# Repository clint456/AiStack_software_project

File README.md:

# 毕业设计项目：ChatGpt对话机器人
## 参考日本开源项目
> [stack-chan](https://github.com/meganetaaan/stack-chan.git)
>
> [Gpt 对话机器人 AI_StackChan2](https://github.com/robo8080/AI_StackChan2)

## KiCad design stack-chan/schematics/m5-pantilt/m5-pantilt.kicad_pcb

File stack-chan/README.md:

# 堆栈陈

[](https://github.com/meganetaaan/stack-陈/动作/工作流程/build.yml）

[日本语](./README_ja.md)

Stack-chan是一个JavaScript驱动的M5Stack嵌入式超级卡哇伊机器人。

*视频（附英文字幕）：https://youtu.be/fZb_mF08xV0
*官方主题标签：[`#stackchan` | `#ｽﾀｯｸﾁｬﾝ`（日文）](https://twitter.com/search?q=%23stackchan%20OR%20%23%EF%BD%BD%EF%BE%80%EF%BD%AF%EF %BD%B8%EF%BE%81%EF%BD%AC%EF%BE%9D）。

＃＃ 特征

*:neutral_face: 显示可爱的脸
*:smile: 表情（高兴、生气、悲伤等）
*:smiley_cat: 自定义脸部
*:眼睛：扫视/凝视/凝视
*:speech_balloon: 说些话
*:灯泡: 插件 M5Units
*:cyclone: 驱动串行(TTL)/PWM伺服系统
*:game_die: 自己制作应用程序

＃＃ 内容

该存储库包含机器人的所有组件。

*__firmware__ : 固件的源代码。
*__case__ ：案例的立体光刻（STL）。
*__schematics__ ：原理图和电路板布局数据。

＃＃ 安装

### 组装板

*请参阅 [schematics/README.md](./schematics/README.md) 和 [case/README.md](./case/README.md)
*或者您可以获得预组装模块（即将推出）
### 将固件闪存到 M5Stack

*请参阅[固件/README.md](./firmware/README.md)

＃＃ 贡献

__功能请求/错误报告__非常受欢迎！请参阅[问题](https://github.com/meganetaaan/stack-chan/issues)页面来发布一些内容。

__想成为赞助商__吗？这将是我莫大的荣幸。请访问我的[赞助商](https://github.com/sponsors/meganetaaan/) 页面。

＃＃ 执照

该存储库的资源根据 Apache 2.0 版许可证分发。
请参阅[许可证](./许可证)。

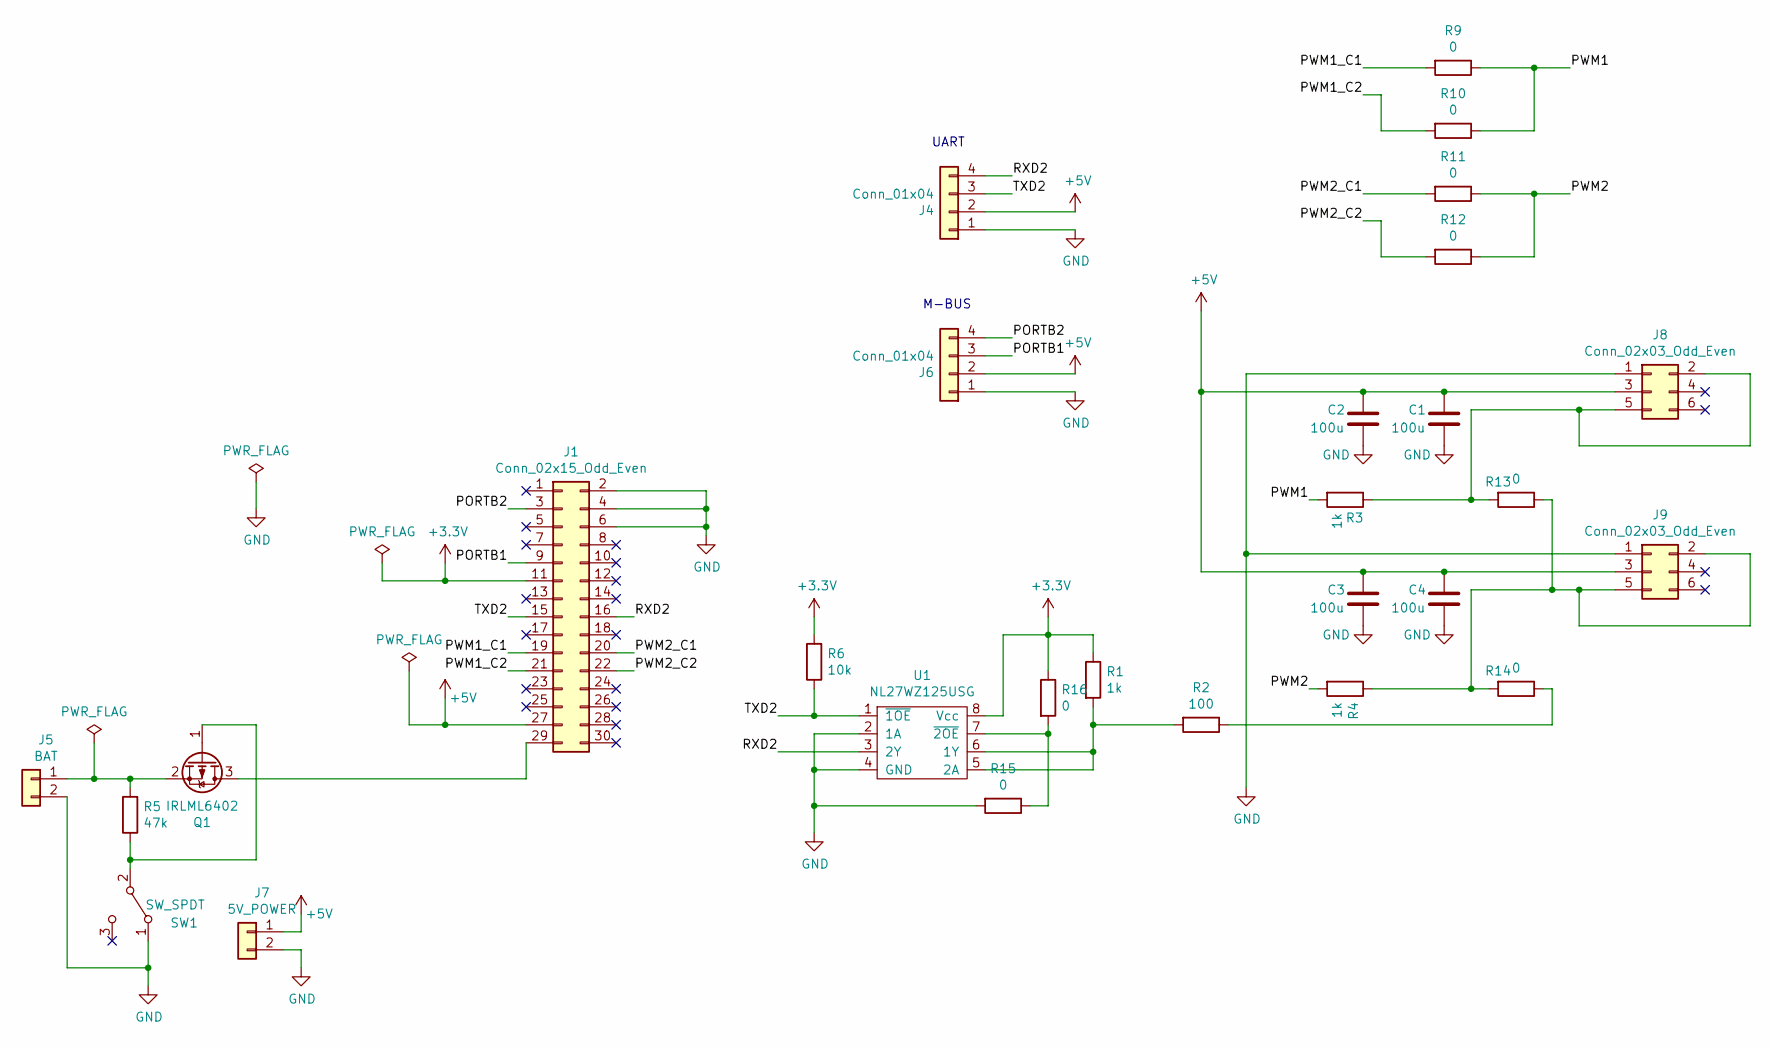
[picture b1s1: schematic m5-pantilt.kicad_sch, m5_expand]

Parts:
C1, C2, C3, C4: 100u; C_1206_3216Metric_Pad1.42x1.75mm_HandSolder
J1: Conn_02x15_Odd_Even; PinHeader_2x15_P2.54mm_Vertical_SMD
J4, J6: Conn_01x04; JST_PH_S4B-PH-K_1x04_P2.00mm_Horizontal
J5: BAT; JST_PH_B2B-PH-K_1x02_P2.00mm_Vertical
J7: 5V_POWER; JST_XH_B2B-XH-A_1x02_P2.50mm_Vertical
J8, J9: Conn_02x03_Odd_Even; PinHeader_2x03_P2.54mm_Vertical
Q1: IRLML6402; SOT-23
R1, R3, R4: 1k; R_0603_1608Metric_Pad1.05x0.95mm_HandSolder
R2: 100; R_0603_1608Metric_Pad1.05x0.95mm_HandSolder
R5: 47k; R_0603_1608Metric_Pad1.05x0.95mm_HandSolder
R6: 10k; R_0603_1608Metric_Pad1.05x0.95mm_HandSolder
R9, R10, R11, R12, R13, R14, R15, R16: 0; R_0603_1608Metric_Pad1.05x0.95mm_HandSolder
SW1: SW_SPDT; SW_CuK_OS102011MA1QN1_SPDT_Angled
U1: NL27WZ125USG

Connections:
+3V3: J1.11, R1.1, R6.2, R16.1, U1.8 (Vcc)
+5V: C1.2, C2.2, C3.1, C4.2, J1.27, J4.2, J6.2, J7.1, J8.3, J9.3; also elsewhere on the board
/PORTB1: J1.9, J6.3
/PORTB2: J1.3, J6.4
/PWM1: R3.2, R9.1, R10.1
/PWM1_C1: J1.19, R9.2
/PWM1_C2: J1.21, R10.2
/PWM2: R4.2, R11.1, R12.1
/PWM2_C1: J1.20, R11.2
/PWM2_C2: J1.22, R12.2
/RXD2: J1.16, J4.4, U1.3 (2Y)
/TXD2: J1.15, J4.3, R6.1, U1.1 (~1OE)
GND: C1.1, C2.1, C3.2, C4.1, J1.2, J1.4, J1.6, J4.1, J5.2, J6.1, J7.2, J8.1, J9.1, R15.2, SW1.1 (A), U1.2 (1A), U1.4 (GND); also elsewhere on the board
unnamed: J1.29, Q1.3 (D)
unnamed 14: J8.2, J8.5, R3.1, R13.2; also elsewhere on the board
unnamed 15: J9.2, J9.5, R4.1, R13.1, R14.2; also elsewhere on the board
unnamed: J5.1, Q1.2 (S), R5.2
unnamed: Q1.1 (G), R5.1, SW1.2 (B)
unnamed: R2.1, R14.1
unnamed: R1.2, R2.2, U1.5 (2A), U1.6 (1Y)
unnamed: R15.1, R16.2, U1.7 (~2OE)

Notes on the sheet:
M-BUS
UART

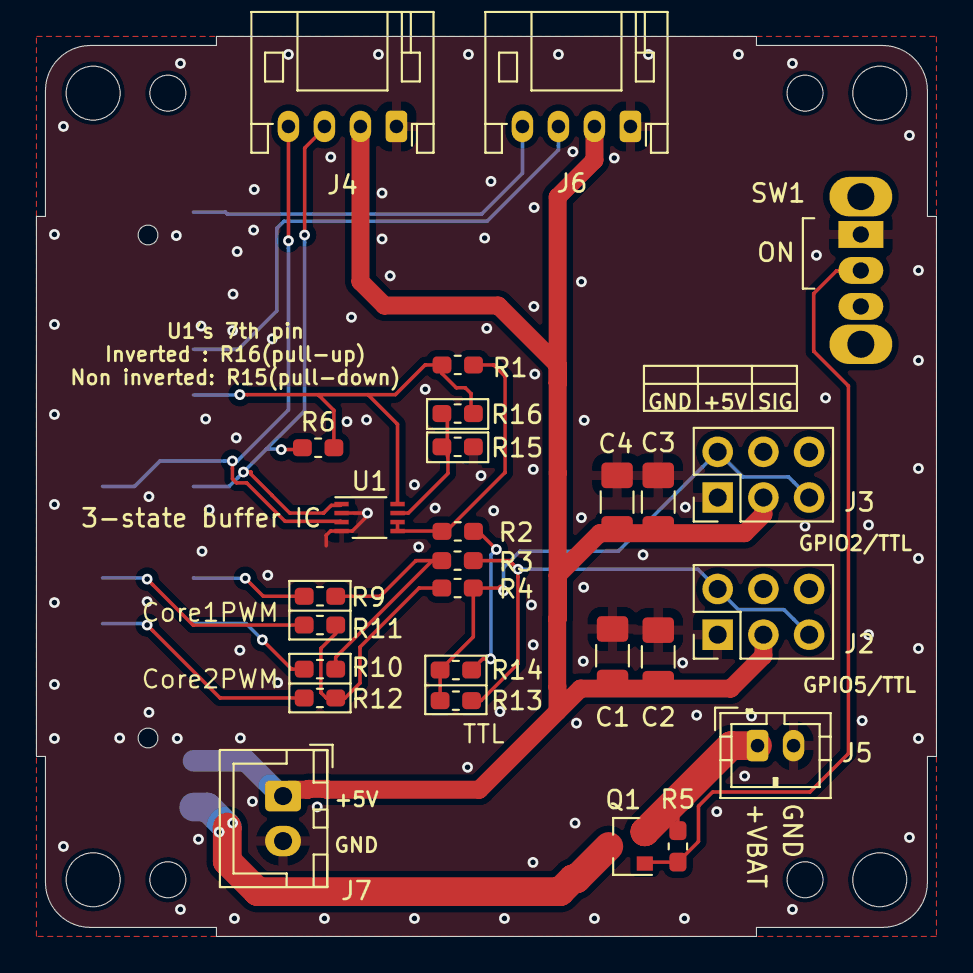
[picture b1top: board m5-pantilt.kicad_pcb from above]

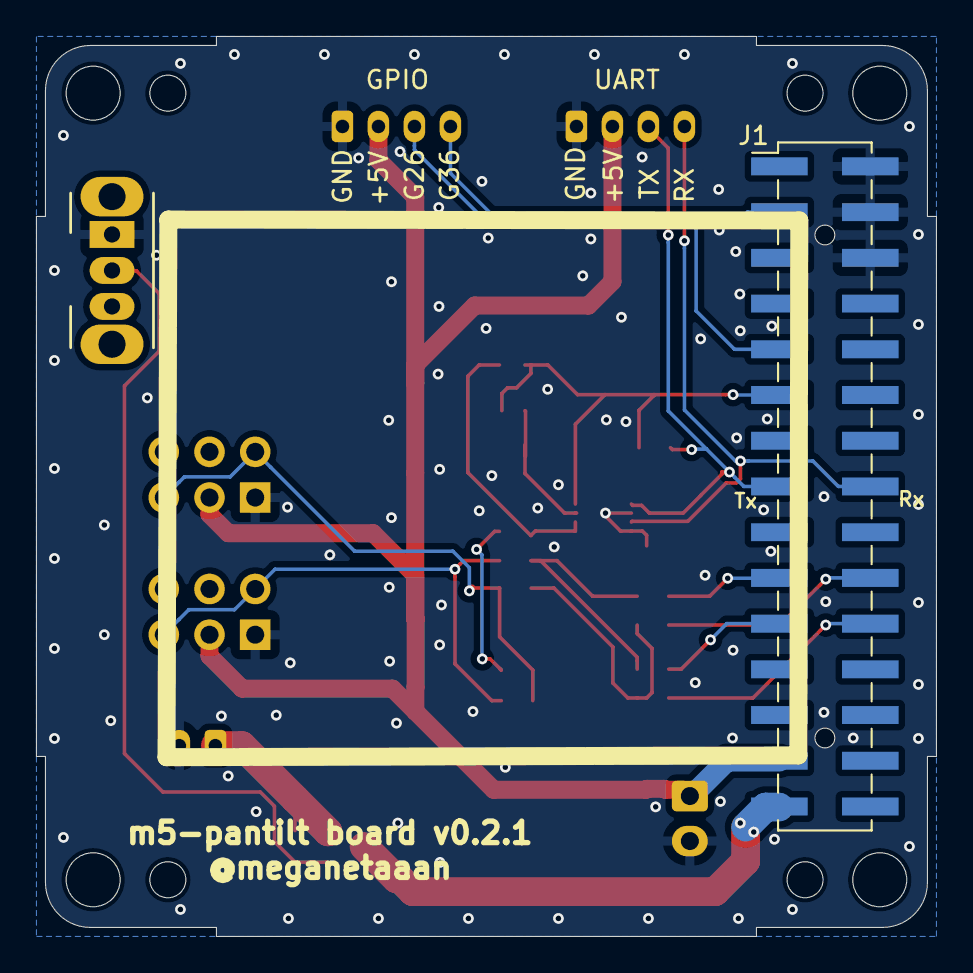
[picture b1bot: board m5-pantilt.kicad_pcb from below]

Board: 2 copper layers, 50.0 x 50.0 mm, 32 parts (2 on the bottom side), 21 nets.

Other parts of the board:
Hole1, Hole2, Hole3, Hole4: mountinghole_M2_M3
J2, J3: Conn_02x03_Odd_Even; PinHeader_2x03_P2.54mm_Vertical

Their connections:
+5V: J2.3, J3.3; also elsewhere on the board
GND: J2.1, J3.1; also elsewhere on the board
unnamed 14: J2.2, J2.5; also elsewhere on the board
unnamed 15: J3.2, J3.5; also elsewhere on the board

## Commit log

2024-03-02 combination

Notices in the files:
parts and their libraries:
Copyright 2021 Accelerated Designs. All rights reserved.
